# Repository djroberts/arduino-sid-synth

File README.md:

####References:

http://www.midibox.org/dokuwiki/lib/exe/fetch.php?media=mb-6582:mb-6582_base_pcb_r2_color.pdf
https://www.arduino.cc/en/Tutorial/Foundations/ShiftOut  
http://www.scale-n.nl/ScaleN_Naslag_Arduino_IC_Integrated_Circuit_74HC595N_DIP_16.aspx  
https://lastminuteengineers.com/74hc595-shift-register-arduino-tutorial/  
http://www.deblauweschicht.nl/tinkering/mos6581_1.html  
http://www.ucapps.de/mbhp/mbhp_sid_v3.pdf  
https://gr33nonline.wordpress.com/2018/11/11/chiptunes/  
http://archive.6502.org/datasheets/mos_6581_sid.pdf
http://www.esp8266learning.com/using-74hc595-shift-register-wemos.php

####Eagle Libraries:

https://github.com/sparkfun/SparkFun-Eagle-Libraries/blob/master/SparkFun-Boards.lbr  
https://github.com/zumbik/Eagle-Libraries/tree/master/gm

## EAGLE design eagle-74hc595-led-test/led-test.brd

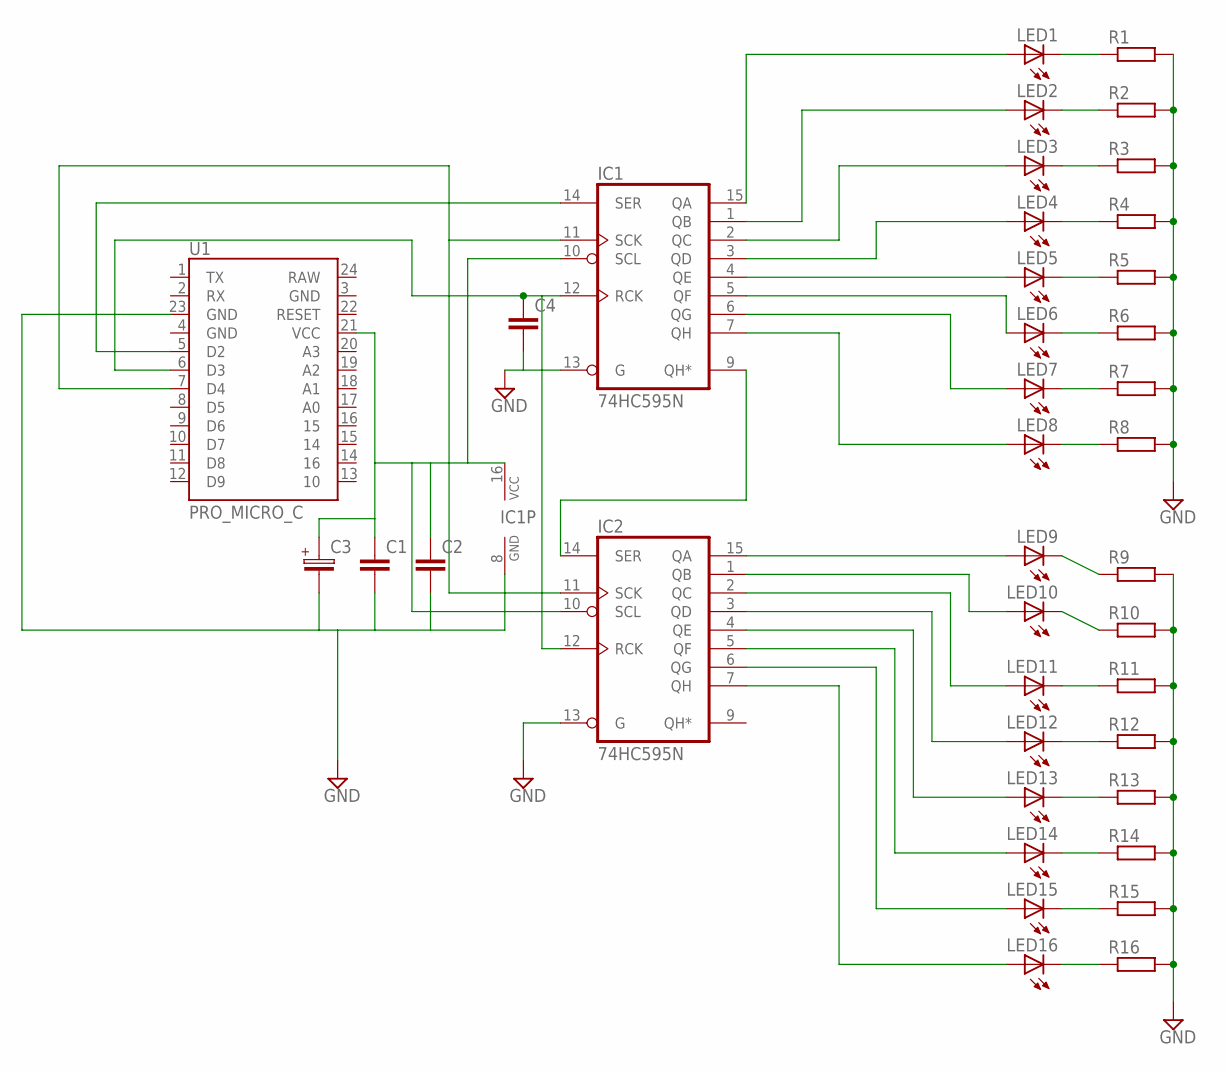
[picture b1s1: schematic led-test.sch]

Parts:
C1, C2, C4: 072X0252; 072X025
C3: 050-EU; 050_020
IC1, IC2: 74HC595N; DIL16
LED1, LED2, LED3, LED4, LED5, LED6, LED7, LED8, LED9, LED10, LED11, LED12, LED13, LED14, LED15, LED16: LED; SMARTLED-TTW
R1, R2, R3, R4, R5, R6, R7, R8, R9, R10, R11, R12, R13, R14, R15, R16: R-EU_0204/7; 0204/7
U1: PRO_MICRO_C

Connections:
GND: C1.2, C2.2, C3.-, C4.2, IC1.8 (GND), IC1.13 (G), IC2.8 (GND), IC2.13 (G), R1.2, R2.2, R3.2, R4.2, R5.2, R6.2, R7.2, R8.2, R9.2, R10.2, R11.2, R12.2, R13.2, R14.2, R15.2, R16.2, U1.23 (GND)
unnamed: C4.1, IC1.12 (RCK), IC2.12 (RCK), U1.6 (D3)
unnamed: IC1.14 (SER), U1.5 (D2)
unnamed: IC1.11 (SCK), IC2.11 (SCK), U1.7 (D4)
unnamed: LED1.C@1 (C), R1.1
unnamed: IC1.15 (QA), LED1.A@1 (A)
unnamed: IC1.1 (QB), LED2.A@1 (A)
unnamed: IC1.2 (QC), LED3.A@1 (A)
unnamed: IC1.3 (QD), LED4.A@1 (A)
unnamed: IC1.4 (QE), LED5.A@1 (A)
unnamed: IC1.5 (QF), LED6.A@1 (A)
unnamed: IC1.6 (QG), LED7.A@1 (A)
unnamed: IC1.7 (QH), LED8.A@1 (A)
unnamed: LED2.C@1 (C), R2.1
unnamed: LED3.C@1 (C), R3.1
unnamed: LED4.C@1 (C), R4.1
unnamed: LED5.C@1 (C), R5.1
unnamed: LED6.C@1 (C), R6.1
unnamed: LED7.C@1 (C), R7.1
unnamed: LED8.C@1 (C), R8.1
unnamed: IC1.9 (QH*), IC2.14 (SER)
unnamed: IC2.1 (QB), LED10.A@1 (A)
unnamed: IC2.2 (QC), LED11.A@1 (A)
unnamed: IC2.3 (QD), LED12.A@1 (A)
unnamed: IC2.4 (QE), LED13.A@1 (A)
unnamed: IC2.5 (QF), LED14.A@1 (A)
unnamed: IC2.6 (QG), LED15.A@1 (A)
unnamed: IC2.7 (QH), LED16.A@1 (A)
unnamed: LED9.C@1 (C), R9.1
unnamed: LED10.C@1 (C), R10.1
unnamed: LED11.C@1 (C), R11.1
unnamed: LED12.C@1 (C), R12.1
unnamed: LED13.C@1 (C), R13.1
unnamed: LED14.C@1 (C), R14.1
unnamed: LED15.C@1 (C), R15.1
unnamed: LED16.C@1 (C), R16.1
unnamed: C1.1, C2.1, C3.+, IC1.10 (SCL), IC1.16 (VCC), IC2.10 (SCL), IC2.16 (VCC), U1.21 (VCC)
unnamed: IC2.15 (QA), LED9.A@1 (A)

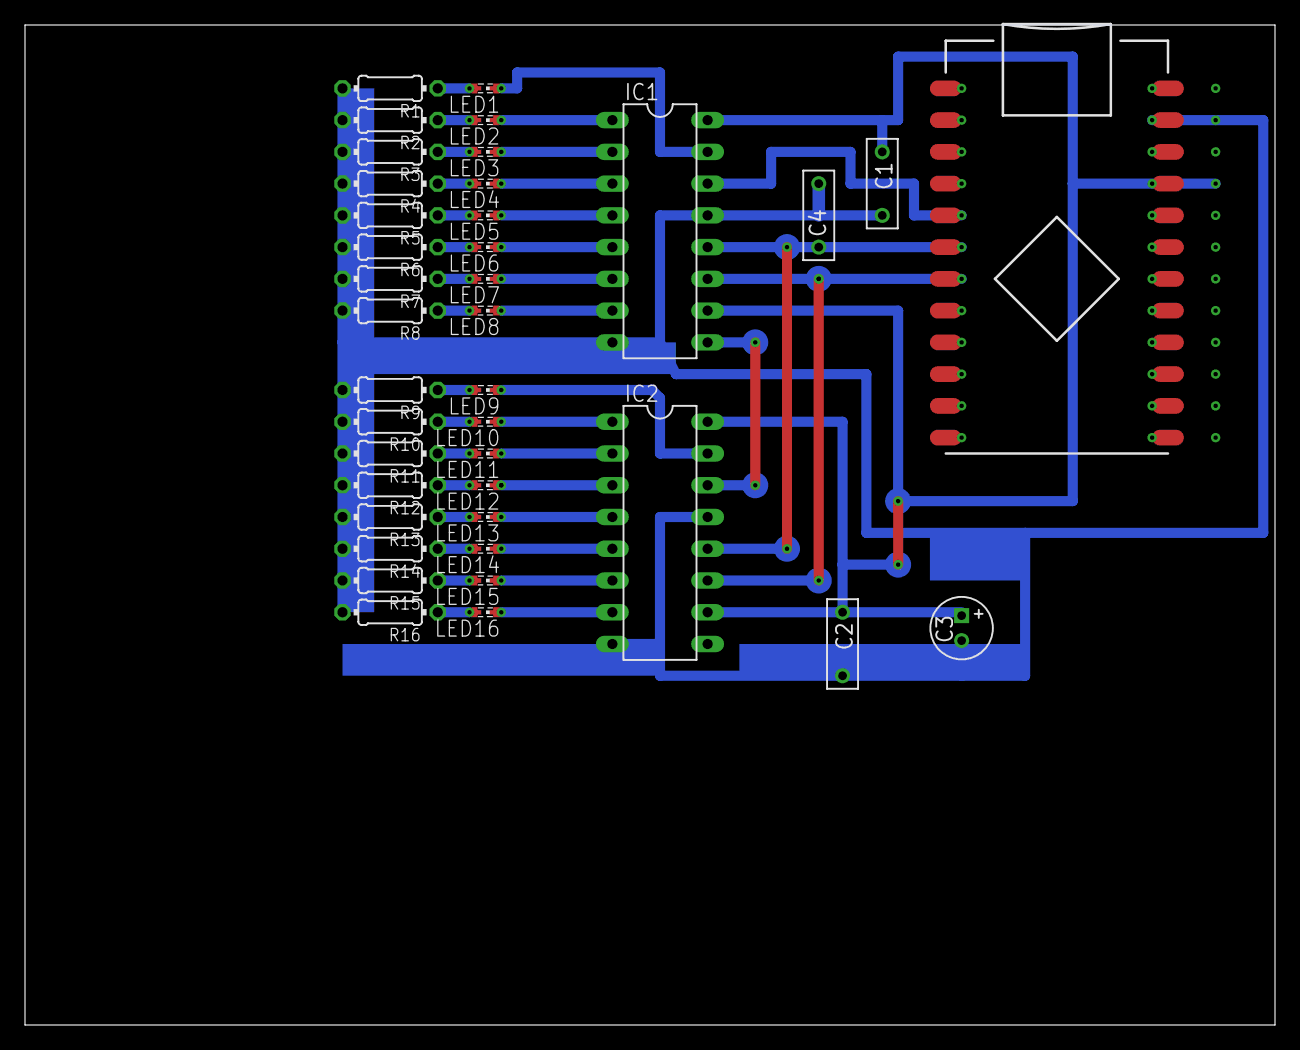
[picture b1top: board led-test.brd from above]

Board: 2 copper layers, 100.0 x 80.0 mm, 39 parts (0 on the bottom side), 38 nets.

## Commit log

2021-02-10 eagle-schematic
2021-02-10 added led test board
2021-02-10 added readme
2021-02-11 readme update
2021-02-14 added cap
2021-03-20 added arduino led tests
2021-03-20 eagle led updates

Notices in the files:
parts and their libraries:
SparkFun-Boards: Licensing: Creative Commons ShareAlike 4.0 International - https://creativecommons.org/licenses/by-sa/4.0
